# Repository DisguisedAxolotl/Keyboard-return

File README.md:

# Keyboard-return
A mechanical keyboard with detachable numpad, OLED displays, rotary encoders, and QMK firmware.

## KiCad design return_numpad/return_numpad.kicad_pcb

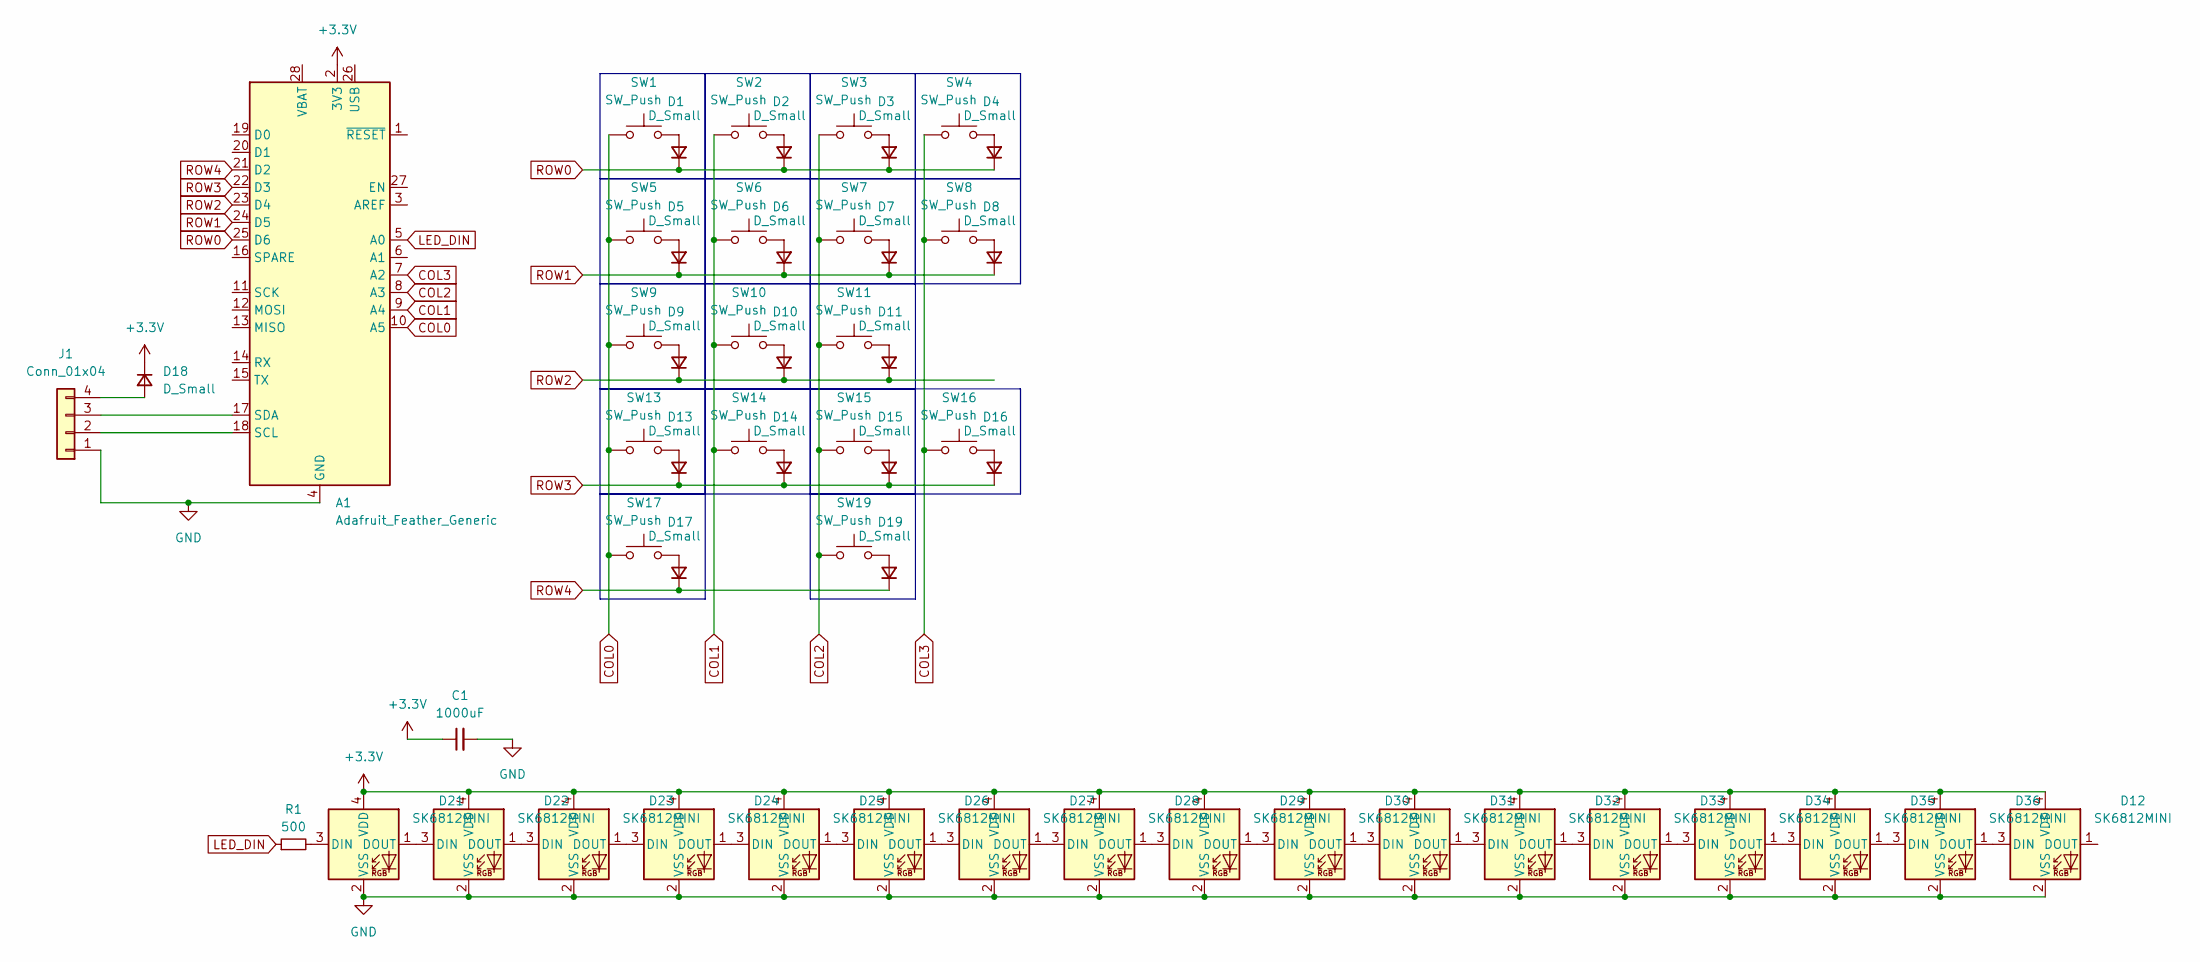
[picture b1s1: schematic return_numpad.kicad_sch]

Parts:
A1: Adafruit_Feather_Generic; Adafruit_Feather
C1: 1000uF; R_Axial_DIN0204_L3.6mm_D1.6mm_P2.54mm_Vertical
D1, D2, D3, D4, D5, D6, D7, D8, D9, D10, D11, D13, D14, D15, D16, D17, D18, D19: D_Small; D_DO-35_SOD27_P7.62mm_Horizontal
D12, D21, D22, D23, D24, D25, D26, D27, D28, D29, D30, D31, D32, D33, D34, D35, D36: SK6812MINI; SK6812-MINI-E
J1: Conn_01x04; PinHeader_1x04_P2.54mm_Vertical
R1: 500; R_Axial_DIN0207_L6.3mm_D2.5mm_P7.62mm_Horizontal
SW1, SW2, SW3, SW4, SW5, SW6, SW7, SW8, SW9, SW10, SW11, SW13, SW14, SW15, SW16, SW17, SW19: SW_Push; Kailh-PG1353-Hotswap-1U

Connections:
+3.3V: A1.2 (3V3), C1.1, D12.4 (VDD), D18.1 (K), D21.4 (VDD), D22.4 (VDD), D23.4 (VDD), D24.4 (VDD), D25.4 (VDD), D26.4 (VDD), D27.4 (VDD), D28.4 (VDD), D29.4 (VDD), D30.4 (VDD), D31.4 (VDD), D32.4 (VDD), D33.4 (VDD), D34.4 (VDD), D35.4 (VDD), D36.4 (VDD)
COL0: A1.10 (A5), SW1.1, SW5.1, SW9.1, SW13.1, SW17.1
COL1: A1.9 (A4), SW2.1, SW6.1, SW10.1, SW14.1
COL2: A1.8 (A3), SW3.1, SW7.1, SW11.1, SW15.1, SW19.1
COL3: A1.7 (A2), SW4.1, SW8.1, SW16.1
GND: A1.4 (GND), C1.2, D12.2 (VSS), D21.2 (VSS), D22.2 (VSS), D23.2 (VSS), D24.2 (VSS), D25.2 (VSS), D26.2 (VSS), D27.2 (VSS), D28.2 (VSS), D29.2 (VSS), D30.2 (VSS), D31.2 (VSS), D32.2 (VSS), D33.2 (VSS), D34.2 (VSS), D35.2 (VSS), D36.2 (VSS), J1.1
LED_DIN: A1.5 (A0), R1.1
unnamed: A1.18 (SCL), J1.2
unnamed: A1.17 (SDA), J1.3
unnamed: D1.2 (A), SW1.2
unnamed: D2.2 (A), SW2.2
unnamed: D3.2 (A), SW3.2
unnamed: D4.2 (A), SW4.2
unnamed: D5.2 (A), SW5.2
unnamed: D6.2 (A), SW6.2
unnamed: D7.2 (A), SW7.2
unnamed: D8.2 (A), SW8.2
unnamed: D9.2 (A), SW9.2
unnamed: D10.2 (A), SW10.2
unnamed: D11.2 (A), SW11.2
unnamed: D12.3 (DIN), D36.1 (DOUT)
unnamed: D13.2 (A), SW13.2
unnamed: D14.2 (A), SW14.2
unnamed: D15.2 (A), SW15.2
unnamed: D16.2 (A), SW16.2
unnamed: D17.2 (A), SW17.2
unnamed: D18.2 (A), J1.4
unnamed: D19.2 (A), SW19.2
unnamed: D21.3 (DIN), R1.2
unnamed: D21.1 (DOUT), D22.3 (DIN)
unnamed: D22.1 (DOUT), D23.3 (DIN)
unnamed: D23.1 (DOUT), D24.3 (DIN)
unnamed: D24.1 (DOUT), D25.3 (DIN)
unnamed: D25.1 (DOUT), D26.3 (DIN)
unnamed: D26.1 (DOUT), D27.3 (DIN)
unnamed: D27.1 (DOUT), D28.3 (DIN)
unnamed: D28.1 (DOUT), D29.3 (DIN)
unnamed: D29.1 (DOUT), D30.3 (DIN)
unnamed: D30.1 (DOUT), D31.3 (DIN)
unnamed: D31.1 (DOUT), D32.3 (DIN)
unnamed: D32.1 (DOUT), D33.3 (DIN)
unnamed: D33.1 (DOUT), D34.3 (DIN)
unnamed: D34.1 (DOUT), D35.3 (DIN)
unnamed: D35.1 (DOUT), D36.3 (DIN)
ROW0: A1.25 (D6), D1.1 (K), D2.1 (K), D3.1 (K), D4.1 (K)
ROW1: A1.24 (D5), D5.1 (K), D6.1 (K), D7.1 (K), D8.1 (K)
ROW2: A1.23 (D4), D9.1 (K), D10.1 (K), D11.1 (K)
ROW3: A1.22 (D3), D13.1 (K), D14.1 (K), D15.1 (K), D16.1 (K)
ROW4: A1.21 (D2), D17.1 (K), D19.1 (K)

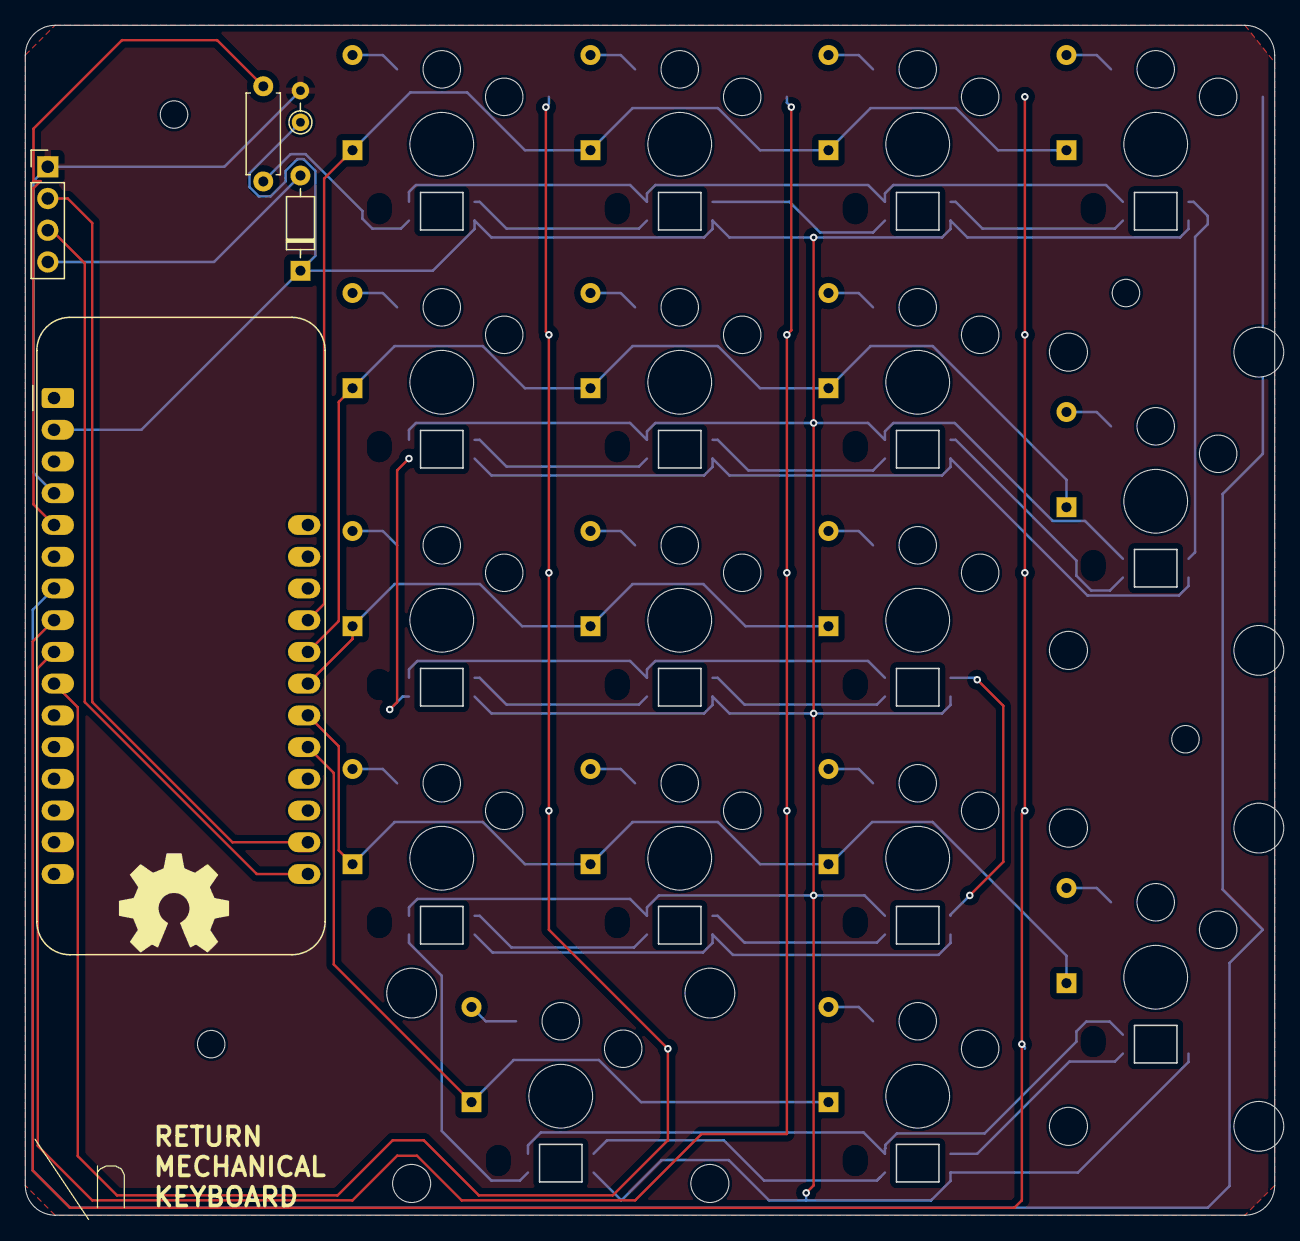
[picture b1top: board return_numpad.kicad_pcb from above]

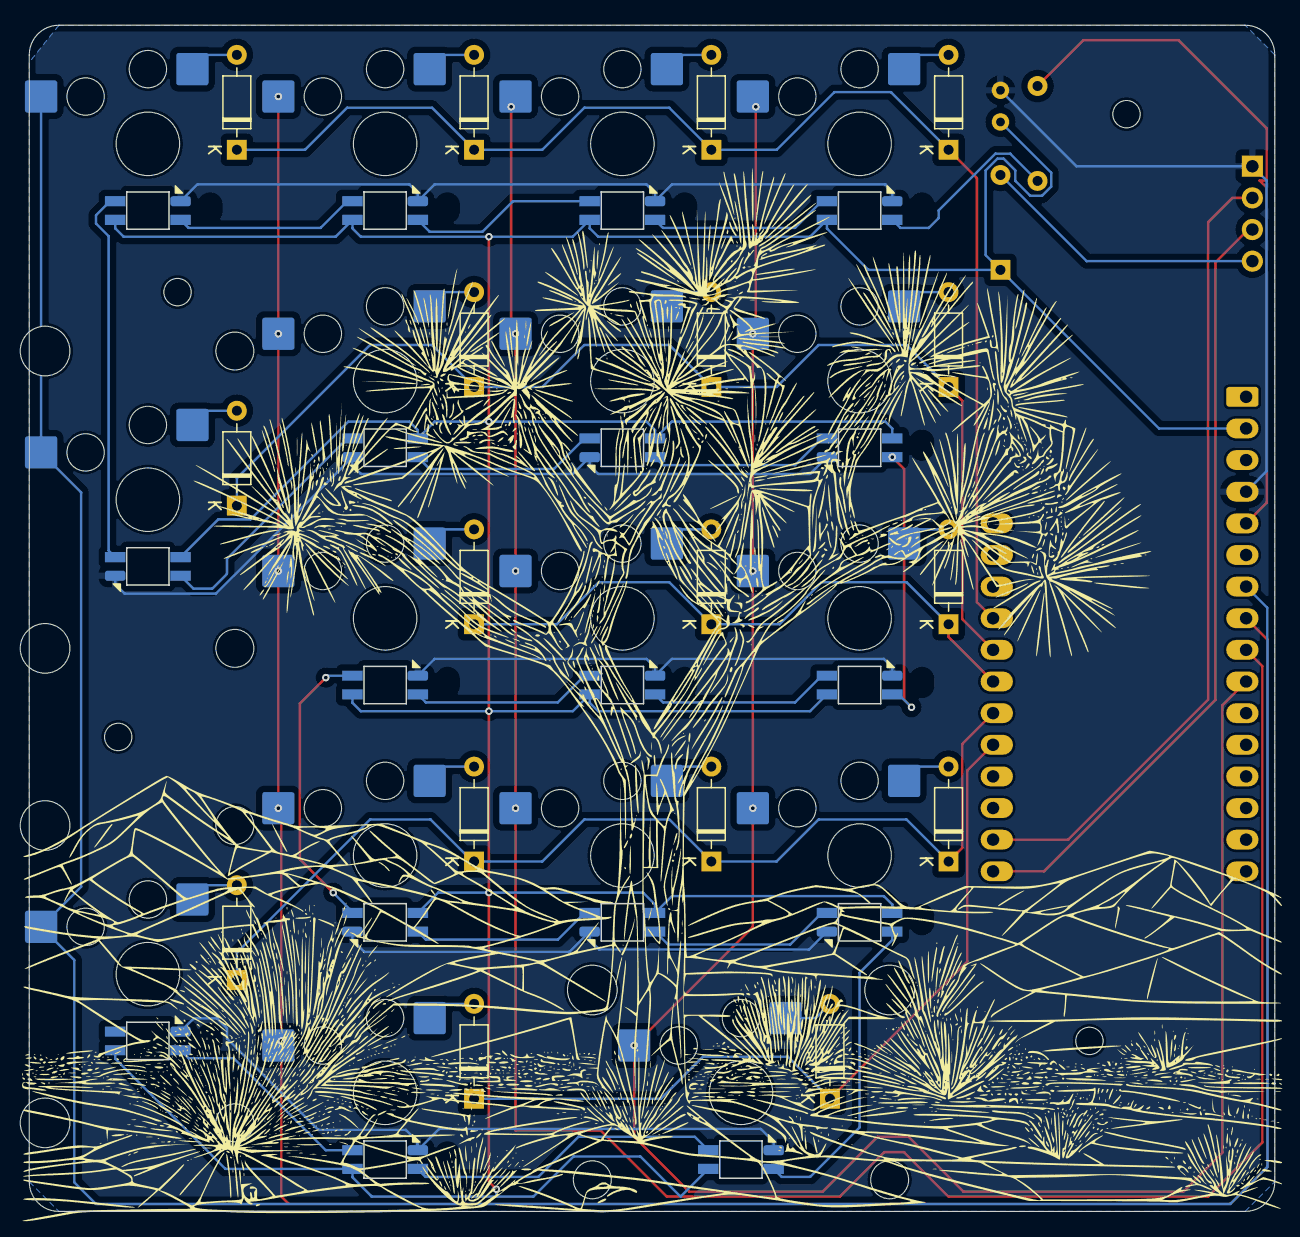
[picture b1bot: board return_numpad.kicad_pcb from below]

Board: 2 copper layers, 99.9 x 95.2 mm, 56 parts (34 on the bottom side), 49 nets.

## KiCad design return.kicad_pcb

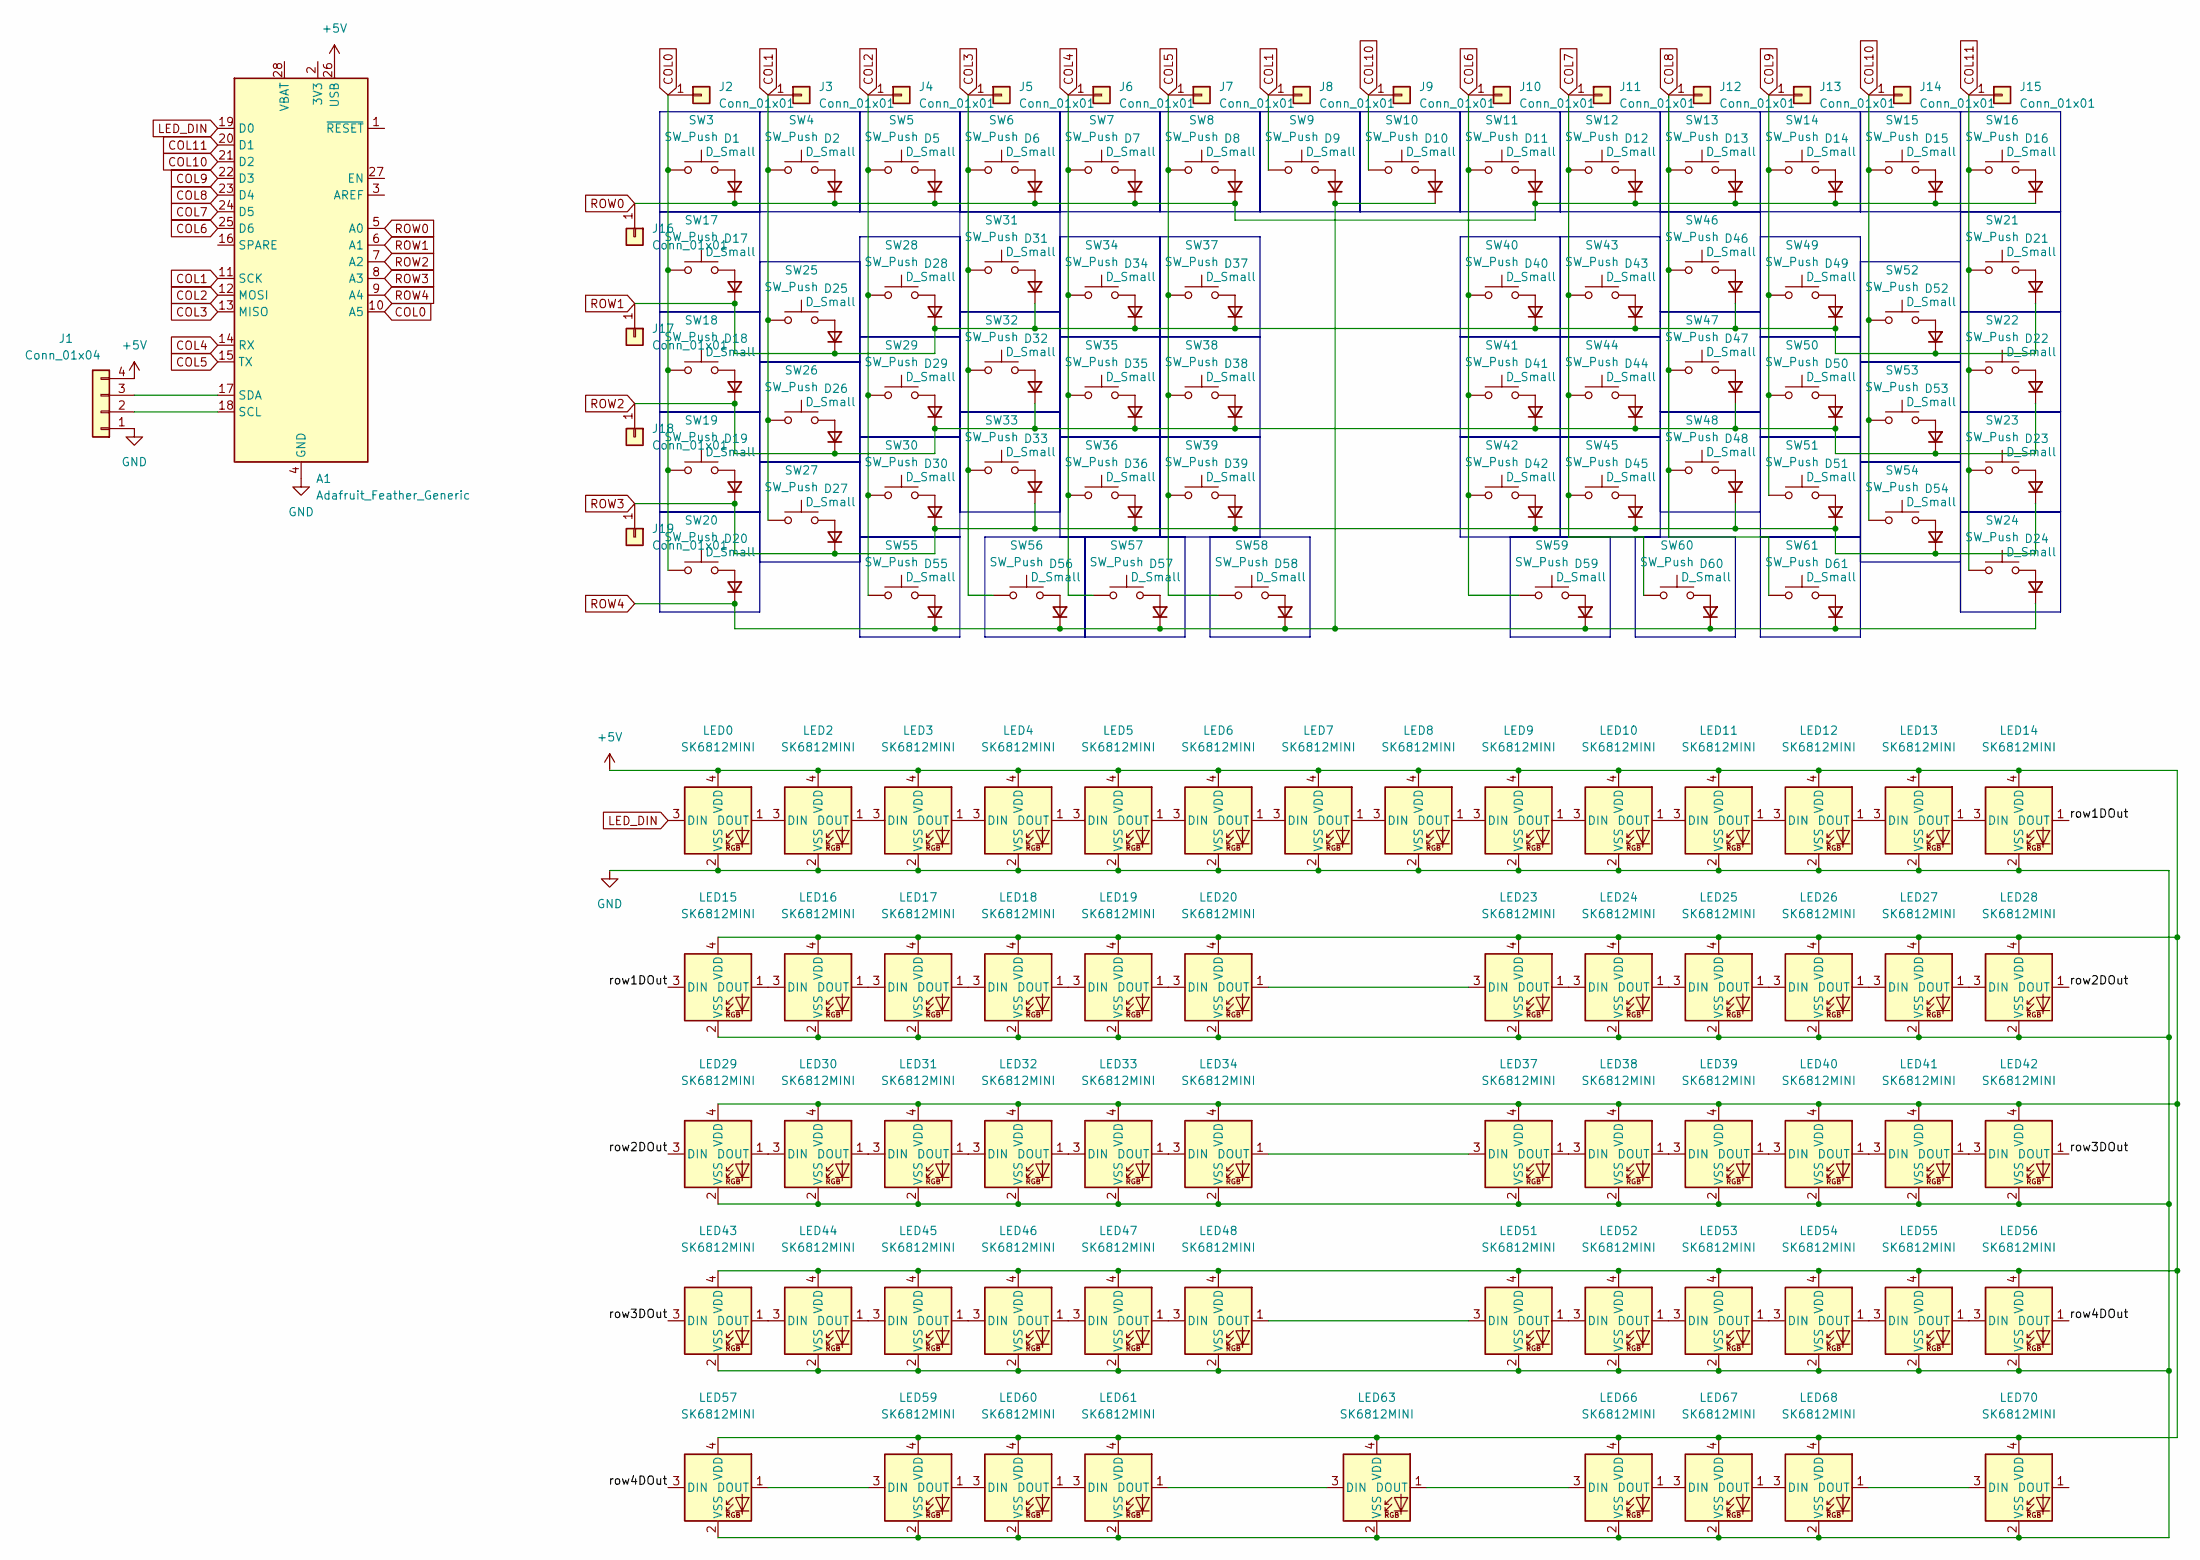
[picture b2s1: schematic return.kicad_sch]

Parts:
A1: Adafruit_Feather_Generic; Adafruit_Feather
D1, D2, D5, D6, D7, D8, D9, D10, D11, D12, D13, D14, D15, D16, D17, D18, D19, D20, D21, D22, D23, D24, D25, D26, D27, D28, D29, D30, D31, D32, D33, D34, D35, D36, D37, D38, D39, D40, D41, D42, D43, D44, D45, D46, D47, D48, D49, D50, D51, D52, D53, D54, D55, D56, D57, D58, D59, D60, D61: D_Small; D_DO-35_SOD27_P7.62mm_Horizontal
J1: Conn_01x04; PinHeader_1x04_P2.54mm_Vertical
J2, J3, J4, J5, J6, J7, J8, J9, J10, J11, J12, J13, J14, J15, J16, J17, J18, J19: Conn_01x01
LED0, LED2, LED3, LED4, LED5, LED6, LED7, LED8, LED9, LED10, LED11, LED12, LED13, LED14, LED15, LED16, LED17, LED18, LED19, LED20, LED23, LED24, LED25, LED26, LED27, LED28, LED29, LED30, LED31, LED32, LED33, LED34, LED37, LED38, LED39, LED40, LED41, LED42, LED43, LED44, LED45, LED46, LED47, LED48, LED51, LED52, LED53, LED54, LED55, LED56, LED57, LED59, LED60, LED61, LED63, LED66, LED67, LED68, LED70: SK6812MINI; SK6812-MINI-E
SW3, SW4, SW5, SW6, SW7, SW8, SW9, SW10, SW11, SW12, SW13, SW14, SW15, SW16, SW17, SW18, SW19, SW20, SW21, SW22, SW23, SW24, SW25, SW26, SW27, SW28, SW29, SW30, SW31, SW32, SW33, SW34, SW35, SW36, SW37, SW38, SW39, SW40, SW41, SW42, SW43, SW44, SW45, SW46, SW47, SW48, SW49, SW50, SW51, SW52, SW53, SW54, SW55, SW56, SW57, SW58, SW59, SW60, SW61: SW_Push; Kailh-PG1353-Hotswap-1U

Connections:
+5V: A1.26 (USB), J1.4, LED0.4 (VDD), LED2.4 (VDD), LED3.4 (VDD), LED4.4 (VDD), LED5.4 (VDD), LED6.4 (VDD), LED7.4 (VDD), LED8.4 (VDD), LED9.4 (VDD), LED10.4 (VDD), LED11.4 (VDD), LED12.4 (VDD), LED13.4 (VDD), LED14.4 (VDD), LED15.4 (VDD), LED16.4 (VDD), LED17.4 (VDD), LED18.4 (VDD), LED19.4 (VDD), LED20.4 (VDD), LED23.4 (VDD), LED24.4 (VDD), LED25.4 (VDD), LED26.4 (VDD), LED27.4 (VDD), LED28.4 (VDD), LED29.4 (VDD), LED30.4 (VDD), LED31.4 (VDD), LED32.4 (VDD), LED33.4 (VDD), LED34.4 (VDD), LED37.4 (VDD), LED38.4 (VDD), LED39.4 (VDD), LED40.4 (VDD), LED41.4 (VDD), LED42.4 (VDD), LED43.4 (VDD), LED44.4 (VDD), LED45.4 (VDD), LED46.4 (VDD), LED47.4 (VDD), LED48.4 (VDD), LED51.4 (VDD), LED52.4 (VDD), LED53.4 (VDD), LED54.4 (VDD), LED55.4 (VDD), LED56.4 (VDD), LED57.4 (VDD), LED59.4 (VDD), LED60.4 (VDD), LED61.4 (VDD), LED63.4 (VDD), LED66.4 (VDD), LED67.4 (VDD), LED68.4 (VDD), LED70.4 (VDD)
/row1DOut: LED14.1 (DOUT), LED15.3 (DIN)
/row2DOut: LED28.1 (DOUT), LED29.3 (DIN)
/row3DOut: LED42.1 (DOUT), LED43.3 (DIN)
/row4DOut: LED56.1 (DOUT), LED57.3 (DIN)
COL0: A1.10 (A5), J2.1, SW3.1, SW17.1, SW18.1, SW19.1, SW20.1
COL1: A1.11 (SCK), J3.1, J8.1, SW4.1, SW9.1, SW25.1, SW26.1, SW27.1
COL2: A1.12 (MOSI), J4.1, SW5.1, SW28.1, SW29.1, SW30.1, SW55.1
COL3: A1.13 (MISO), J5.1, SW6.1, SW31.1, SW32.1, SW33.1, SW56.1
COL4: A1.14 (RX), J6.1, SW7.1, SW34.1, SW35.1, SW36.1, SW57.1
COL5: A1.15 (TX), J7.1, SW8.1, SW37.1, SW38.1, SW39.1, SW58.1
COL6: A1.25 (D6), J10.1, SW11.1, SW40.1, SW41.1, SW42.1, SW59.1
COL7: A1.24 (D5), J11.1, SW12.1, SW43.1, SW44.1, SW45.1, SW60.1
COL8: A1.23 (D4), J12.1, SW13.1, SW46.1, SW47.1, SW48.1, SW61.1
COL9: A1.22 (D3), J13.1, SW14.1, SW49.1, SW50.1, SW51.1
COL10: A1.21 (D2), J9.1, J14.1, SW10.1, SW15.1, SW52.1, SW53.1, SW54.1
COL11: A1.20 (D1), J15.1, SW16.1, SW21.1, SW22.1, SW23.1, SW24.1
GND: A1.4 (GND), J1.1, LED0.2 (VSS), LED2.2 (VSS), LED3.2 (VSS), LED4.2 (VSS), LED5.2 (VSS), LED6.2 (VSS), LED7.2 (VSS), LED8.2 (VSS), LED9.2 (VSS), LED10.2 (VSS), LED11.2 (VSS), LED12.2 (VSS), LED13.2 (VSS), LED14.2 (VSS), LED15.2 (VSS), LED16.2 (VSS), LED17.2 (VSS), LED18.2 (VSS), LED19.2 (VSS), LED20.2 (VSS), LED23.2 (VSS), LED24.2 (VSS), LED25.2 (VSS), LED26.2 (VSS), LED27.2 (VSS), LED28.2 (VSS), LED29.2 (VSS), LED30.2 (VSS), LED31.2 (VSS), LED32.2 (VSS), LED33.2 (VSS), LED34.2 (VSS), LED37.2 (VSS), LED38.2 (VSS), LED39.2 (VSS), LED40.2 (VSS), LED41.2 (VSS), LED42.2 (VSS), LED43.2 (VSS), LED44.2 (VSS), LED45.2 (VSS), LED46.2 (VSS), LED47.2 (VSS), LED48.2 (VSS), LED51.2 (VSS), LED52.2 (VSS), LED53.2 (VSS), LED54.2 (VSS), LED55.2 (VSS), LED56.2 (VSS), LED57.2 (VSS), LED59.2 (VSS), LED60.2 (VSS), LED61.2 (VSS), LED63.2 (VSS), LED66.2 (VSS), LED67.2 (VSS), LED68.2 (VSS), LED70.2 (VSS)
LED_DIN: A1.19 (D0), LED0.3 (DIN)
unnamed: A1.18 (SCL), J1.2
unnamed: A1.17 (SDA), J1.3
unnamed: D1.2 (A), SW3.2
unnamed: D2.2 (A), SW4.2
unnamed: D5.2 (A), SW5.2
unnamed: D6.2 (A), SW6.2
unnamed: D7.2 (A), SW7.2
unnamed: D8.2 (A), SW8.2
unnamed: D9.2 (A), SW9.2
unnamed: D10.2 (A), SW10.2
unnamed: D11.2 (A), SW11.2
unnamed: D12.2 (A), SW12.2
unnamed: D13.2 (A), SW13.2
unnamed: D14.2 (A), SW14.2
unnamed: D15.2 (A), SW15.2
unnamed: D16.2 (A), SW16.2
unnamed: D17.2 (A), SW17.2
unnamed: D18.2 (A), SW18.2
unnamed: D19.2 (A), SW19.2
unnamed: D20.2 (A), SW20.2
unnamed: D21.2 (A), SW21.2
unnamed: D22.2 (A), SW22.2
unnamed: D23.2 (A), SW23.2
unnamed: D24.2 (A), SW24.2
unnamed: D25.2 (A), SW25.2
unnamed: D26.2 (A), SW26.2
unnamed: D27.2 (A), SW27.2
unnamed: D28.2 (A), SW28.2
unnamed: D29.2 (A), SW29.2
unnamed: D30.2 (A), SW30.2
unnamed: D31.2 (A), SW31.2
unnamed: D32.2 (A), SW32.2
unnamed: D33.2 (A), SW33.2
unnamed: D34.2 (A), SW34.2
unnamed: D35.2 (A), SW35.2
unnamed: D36.2 (A), SW36.2
unnamed: D37.2 (A), SW37.2
unnamed: D38.2 (A), SW38.2
unnamed: D39.2 (A), SW39.2
unnamed: D40.2 (A), SW40.2
unnamed: D41.2 (A), SW41.2
unnamed: D42.2 (A), SW42.2
unnamed: D43.2 (A), SW43.2
unnamed: D44.2 (A), SW44.2
unnamed: D45.2 (A), SW45.2
unnamed: D46.2 (A), SW46.2
unnamed: D47.2 (A), SW47.2
unnamed: D48.2 (A), SW48.2
unnamed: D49.2 (A), SW49.2
unnamed: D50.2 (A), SW50.2
unnamed: D51.2 (A), SW51.2
unnamed: D52.2 (A), SW52.2
unnamed: D53.2 (A), SW53.2
unnamed: D54.2 (A), SW54.2
unnamed: D55.2 (A), SW55.2
unnamed: D56.2 (A), SW56.2
unnamed: D57.2 (A), SW57.2
unnamed: D58.2 (A), SW58.2
unnamed: D59.2 (A), SW59.2
unnamed: D60.2 (A), SW60.2
unnamed: D61.2 (A), SW61.2
unnamed: LED0.1 (DOUT), LED2.3 (DIN)
unnamed: LED2.1 (DOUT), LED3.3 (DIN)
unnamed: LED3.1 (DOUT), LED4.3 (DIN)
unnamed: LED4.1 (DOUT), LED5.3 (DIN)
unnamed: LED5.1 (DOUT), LED6.3 (DIN)
unnamed: LED6.1 (DOUT), LED7.3 (DIN)
unnamed: LED7.1 (DOUT), LED8.3 (DIN)
unnamed: LED8.1 (DOUT), LED9.3 (DIN)
unnamed: LED9.1 (DOUT), LED10.3 (DIN)
unnamed: LED10.1 (DOUT), LED11.3 (DIN)
unnamed: LED11.1 (DOUT), LED12.3 (DIN)
unnamed: LED12.1 (DOUT), LED13.3 (DIN)
unnamed: LED13.1 (DOUT), LED14.3 (DIN)
unnamed: LED15.1 (DOUT), LED16.3 (DIN)
unnamed: LED16.1 (DOUT), LED17.3 (DIN)
unnamed: LED17.1 (DOUT), LED18.3 (DIN)
unnamed: LED18.1 (DOUT), LED19.3 (DIN)
unnamed: LED19.1 (DOUT), LED20.3 (DIN)
unnamed: LED20.1 (DOUT), LED23.3 (DIN)
unnamed: LED23.1 (DOUT), LED24.3 (DIN)
unnamed: LED24.1 (DOUT), LED25.3 (DIN)
unnamed: LED25.1 (DOUT), LED26.3 (DIN)
unnamed: LED26.1 (DOUT), LED27.3 (DIN)
unnamed: LED27.1 (DOUT), LED28.3 (DIN)
unnamed: LED29.1 (DOUT), LED30.3 (DIN)
unnamed: LED30.1 (DOUT), LED31.3 (DIN)
unnamed: LED31.1 (DOUT), LED32.3 (DIN)
unnamed: LED32.1 (DOUT), LED33.3 (DIN)
unnamed: LED33.1 (DOUT), LED34.3 (DIN)
unnamed: LED34.1 (DOUT), LED37.3 (DIN)
unnamed: LED37.1 (DOUT), LED38.3 (DIN)
unnamed: LED38.1 (DOUT), LED39.3 (DIN)
unnamed: LED39.1 (DOUT), LED40.3 (DIN)
unnamed: LED40.1 (DOUT), LED41.3 (DIN)
unnamed: LED41.1 (DOUT), LED42.3 (DIN)
unnamed: LED43.1 (DOUT), LED44.3 (DIN)
unnamed: LED44.1 (DOUT), LED45.3 (DIN)
unnamed: LED45.1 (DOUT), LED46.3 (DIN)
unnamed: LED46.1 (DOUT), LED47.3 (DIN)
unnamed: LED47.1 (DOUT), LED48.3 (DIN)
unnamed: LED48.1 (DOUT), LED51.3 (DIN)
unnamed: LED51.1 (DOUT), LED52.3 (DIN)
unnamed: LED52.1 (DOUT), LED53.3 (DIN)
unnamed: LED53.1 (DOUT), LED54.3 (DIN)
unnamed: LED54.1 (DOUT), LED55.3 (DIN)
unnamed: LED55.1 (DOUT), LED56.3 (DIN)
unnamed: LED57.1 (DOUT), LED59.3 (DIN)
unnamed: LED59.1 (DOUT), LED60.3 (DIN)
unnamed: LED60.1 (DOUT), LED61.3 (DIN)
unnamed: LED61.1 (DOUT), LED63.3 (DIN)
unnamed: LED63.1 (DOUT), LED66.3 (DIN)
unnamed: LED66.1 (DOUT), LED67.3 (DIN)
unnamed: LED67.1 (DOUT), LED68.3 (DIN)
unnamed: LED68.1 (DOUT), LED70.3 (DIN)
ROW0: A1.5 (A0), D1.1 (K), D2.1 (K), D5.1 (K), D6.1 (K), D7.1 (K), D8.1 (K), D11.1 (K), D12.1 (K), D13.1 (K), D14.1 (K), D15.1 (K), D16.1 (K), J16.1
ROW1: A1.6 (A1), D17.1 (K), D21.1 (K), D25.1 (K), D28.1 (K), D31.1 (K), D34.1 (K), D37.1 (K), D40.1 (K), D43.1 (K), D46.1 (K), D49.1 (K), D52.1 (K), J17.1
ROW2: A1.7 (A2), D18.1 (K), D22.1 (K), D26.1 (K), D29.1 (K), D32.1 (K), D35.1 (K), D38.1 (K), D41.1 (K), D44.1 (K), D47.1 (K), D50.1 (K), D53.1 (K), J18.1
ROW3: A1.8 (A3), D19.1 (K), D23.1 (K), D27.1 (K), D30.1 (K), D33.1 (K), D36.1 (K), D39.1 (K), D42.1 (K), D45.1 (K), D48.1 (K), D51.1 (K), D54.1 (K), J19.1
ROW4: A1.9 (A4), D9.1 (K), D10.1 (K), D20.1 (K), D24.1 (K), D55.1 (K), D56.1 (K), D57.1 (K), D58.1 (K), D59.1 (K), D60.1 (K), D61.1 (K)

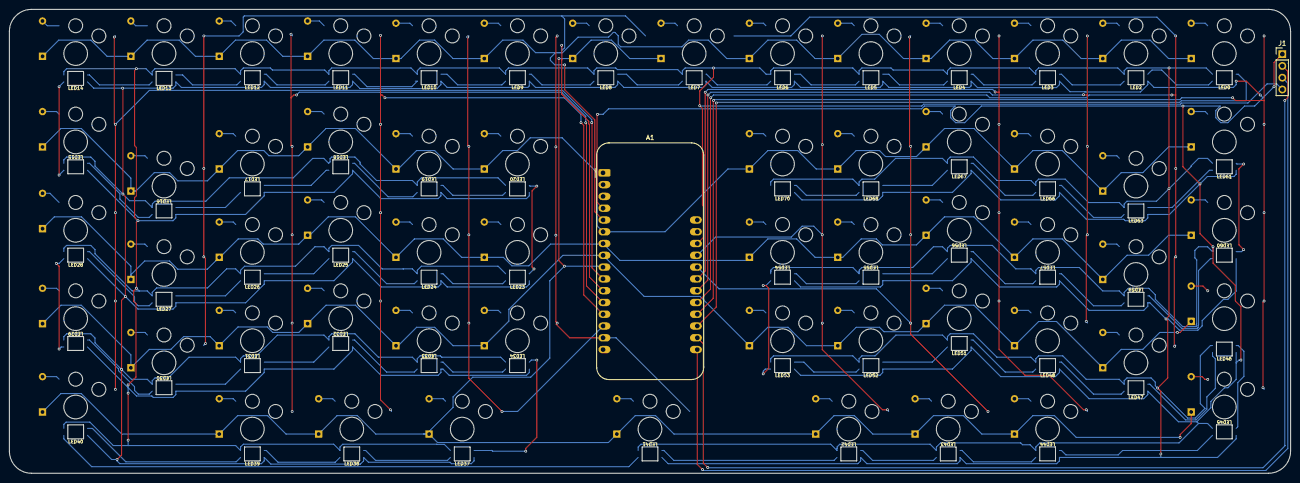
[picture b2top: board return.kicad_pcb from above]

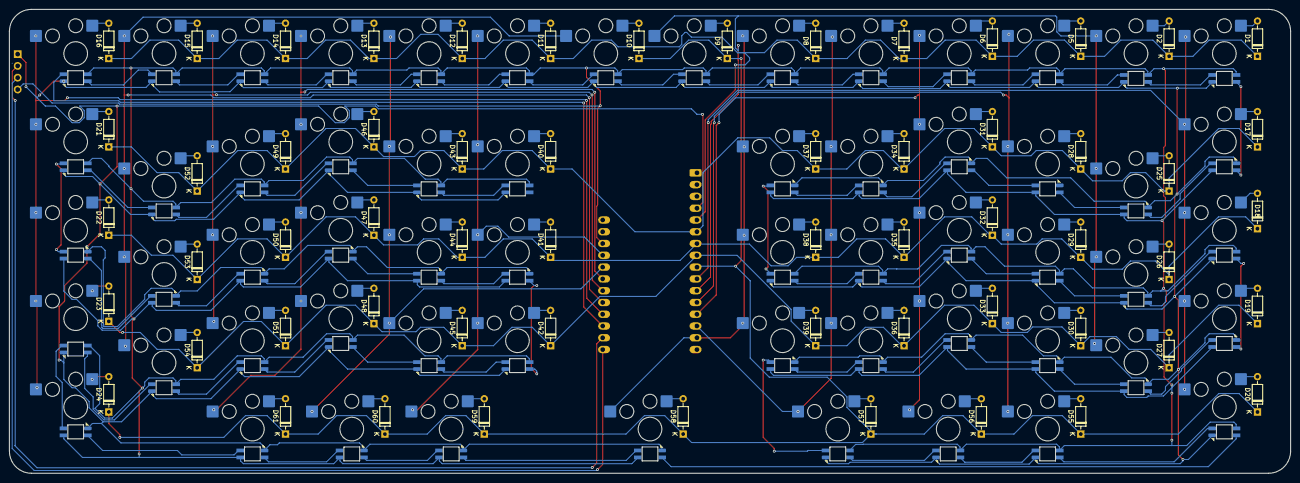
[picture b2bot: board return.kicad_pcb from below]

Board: 2 copper layers, 276.2 x 99.9 mm, 179 parts (118 on the bottom side), 139 nets.

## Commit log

2024-10-15 Add empty kicad project, add Adafruit feather schematic
2024-10-21 Add keyboard-layout-editor json
2024-10-29 Revise Schematic
2024-11-08 add project for numpad, finish PCB routing.
2024-11-13 Finish main schematic, finish aux schematic, add production files.
